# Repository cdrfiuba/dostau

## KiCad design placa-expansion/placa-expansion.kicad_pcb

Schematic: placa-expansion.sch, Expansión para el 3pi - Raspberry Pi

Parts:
C1: 2.2uF
C2: 330uF
D1: LED
J1: PBD-26
JP1: JUMPER
P1: BATT
P2: CONN_3PI
P3: PWR_HUB
P4: PWR_3pi
P5, P6, P7, P8: CONN_4
R1: 21k
R2: 330
U1: PTN78020
U?1: TXB0108

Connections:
+5V: C2.1, J1.2 (5v), P3.2 (PM), P5.1, P6.1, P7.1, P8.1, U1.5 (Vos), U1.6 (VO)
+BATT: C1.1, P1.2 (PM), P4.2 (PM), U1.2 (VI)
/3v3_rPi: J1.1 (3v3), U?1.2 (VCCA), U?1.10 (OE)
/AD6: P2.8, P5.3, U?1.17 (B3)
/AD6_rPi: J1.11 (GPIO17), U?1.4 (A3)
/AD7: P2.10, P6.3, U?1.16 (B4)
/AD7_rPi: J1.13 (GPIO21), U?1.5 (A4)
/Echo3: P2.12, P7.3, U?1.15 (B5)
/Echo4: P2.11, P8.3, U?1.14 (B6)
/LED: J1.23 (GPIO11/SCLK), U?1.9 (A8)
/PB3_rPi: J1.21 (GPIO9/MISO), U?1.8 (A7)
/PC5_rPi: J1.15 (GPIO22), U?1.6 (A5)
/PC6: P2.9, P5.2, P6.2, P7.2, P8.2, U?1.13 (B7)
/PC6_rPi: J1.19 (GPIO10/MOSI), U?1.7 (A6)
/RX_3pi: P2.4, U?1.20 (B1)
/RX_rPi: J1.10 (GPIO15/Rx), U?1.3 (A2)
/TX_3pi: P2.6, U?1.18 (B2)
/VBoost: P2.3
/Vbat_3pi: P2.5
/Vcc_3pi: P2.7, U?1.19 (VCCB)
GND: C1.2, C2.2, J1.6 (GND), JP1.2, P1.1, P2.1, P2.2, P2.13, P2.14, P3.1, P4.1, P5.4, P6.4, P7.4, P8.4, R2.1, U1.1 (GND), U?1.11 (GND)
unnamed: R1.2, U1.4 (set1)
unnamed: R1.1, U1.7 (GND)
unnamed: D1.2 (K), R2.2
unnamed: D1.1 (A), U?1.12 (B8)
unnamed: JP1.1, U1.3 (Inhibit)

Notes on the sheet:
Conector rPi
HC-SR04 UltraSound Pingers
3pi expansion
Fuente

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
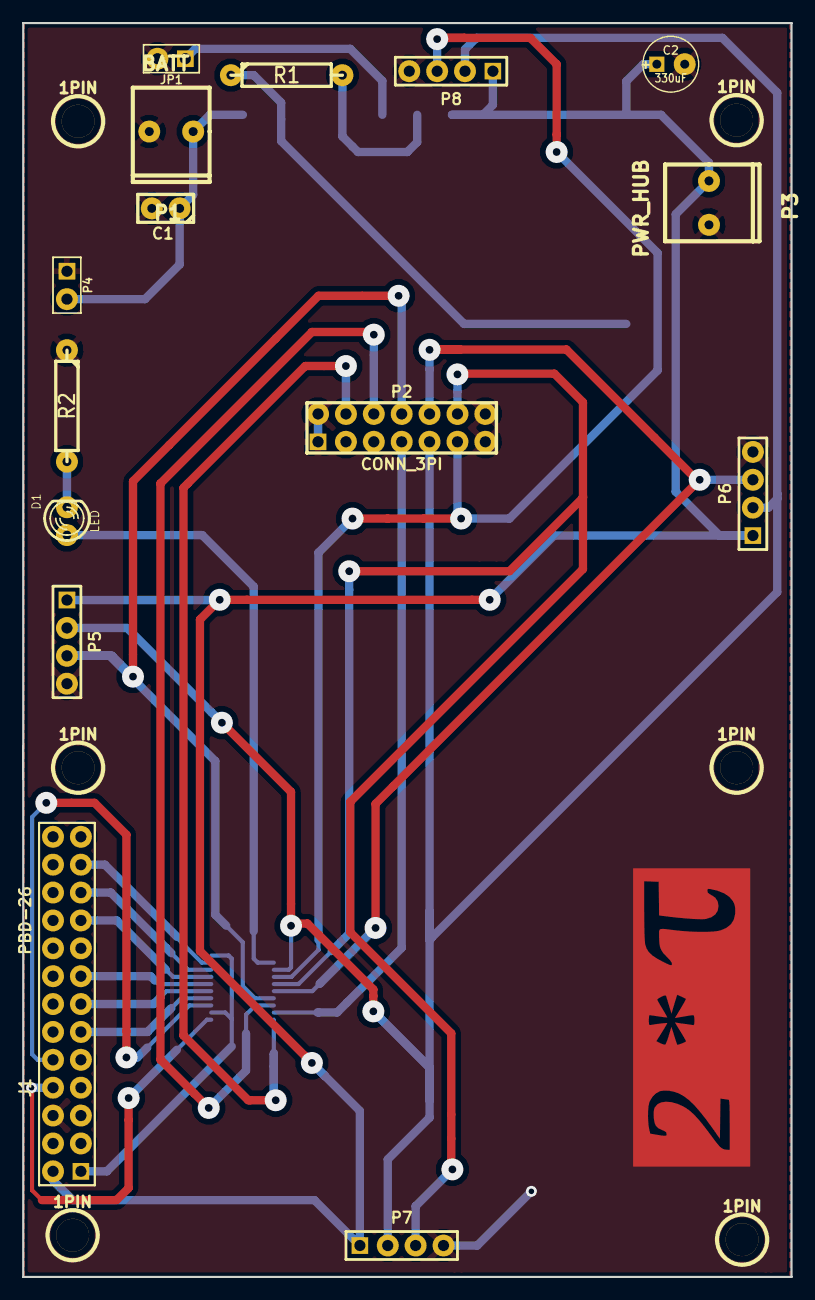
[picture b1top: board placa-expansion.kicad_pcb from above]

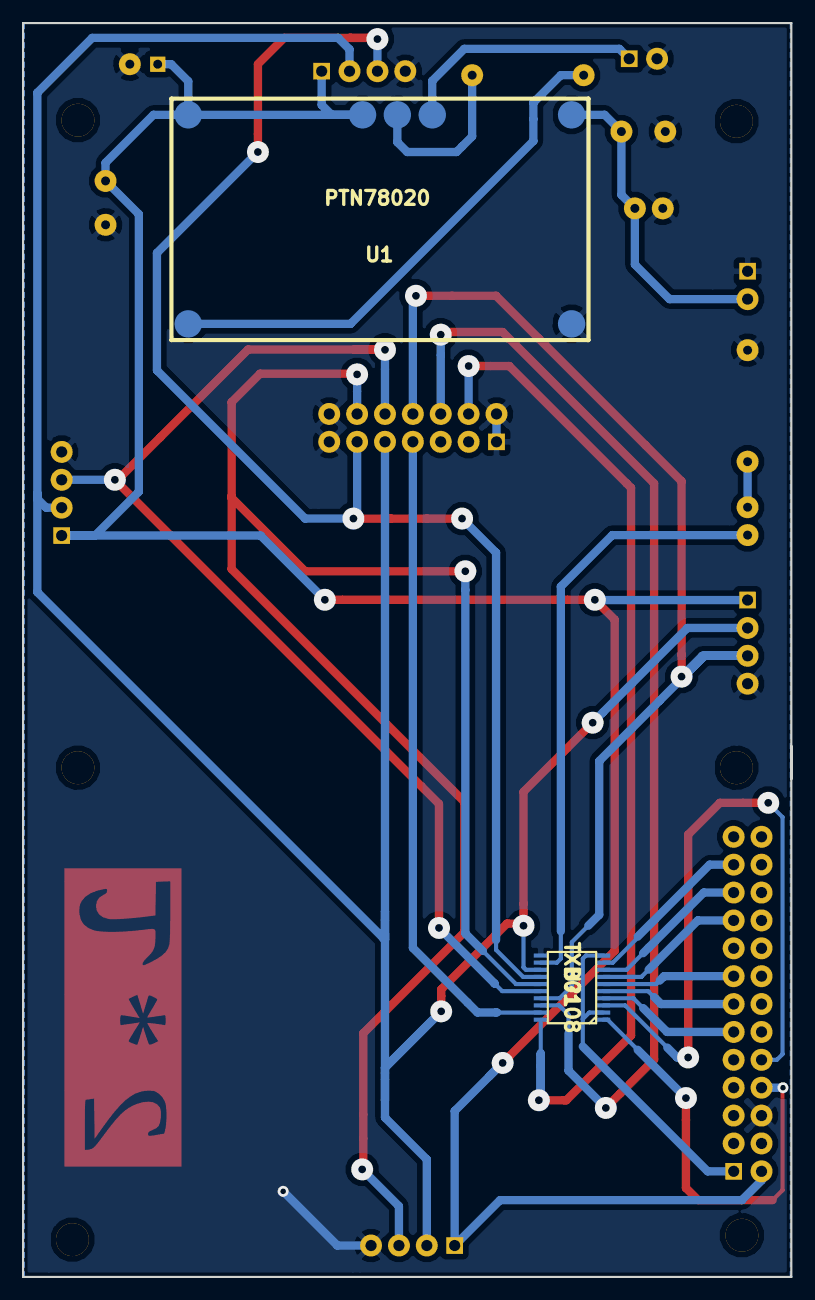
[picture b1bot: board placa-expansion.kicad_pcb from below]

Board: 2 copper layers, 70.0 x 114.2 mm, 23 parts (2 on the bottom side), 25 nets.

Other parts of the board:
1PIN, 1PIN#2, 1PIN#3, 1PIN#4, 1PIN#5, 1PIN#6: P***; 1pin

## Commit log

2013-04-21 Creo el proyecto de Kicad y agrego el componente con el conector de la rPi.
2013-04-26 Se incluye los ejemplos de pololu para el 3pi. El micro es el avr328p y el ejemplo utilizar es 3pi-demo-or-serial-slave
2013-04-27 Agregamos los conectores al esquematico.
    Falta poner la interfaz en los pines Tx y Rx entre el 3pi y el rPi.
    Falta tambien agregar el regulador para la rPi.
2013-04-27 El driver que utilizaremos para interfacear el rPi con el 3pi es el TXB0108
2013-05-04 Se trabajo sobre el esquemático
    Se agrego el integrado buffer y el regulador de 5V para la rPi
2013-05-10 Revisamos el esquematico.
    Faltan agregar los sensores.
2013-05-11 Terminamos el esquemático. Saco dos archivos que no tenian que estar.
2013-05-11 Asociamos los componentes del esquematico a su footprint
2013-05-11 Agregamos los footprint del regulador de texas
2013-05-18 Se terminó de asignar los footprints a todos los componentes y se comenzó con el ruteo de la placa
2013-05-25 Agrego el principio de la implementacion del protocolo para comunicarse con el 3pi desde la rPi usando el puerto serie.
2013-05-26 Agrego el .hgignore.
2013-05-26 Casi terminado el modulo de comunicacion serie con el 3pi. Faltan las funciones que leen datos del auto.
2013-05-26 Renombre la biblioteca a Py3pi en lugar de m3pi.
2013-05-26 Completo la implementacion del protocolo. Hay unos cuentos tests pero faltan algunos. 89% de coverage.
2013-05-26 Empaqueto el modulo de comunicacion serie con dist-utils para simplificar su posterior uso.
2013-05-29 Renombro src a Py3pi.
2013-05-29 Agrego imagenes de prueba y archivos de segmentos correspondientes. Agregamos clase python de lineas.
2013-05-29 Agrego un experimento para procesar los segmentos de lineas.
2013-05-30 Ordeno los vértices de cada segmento según su coordenada Y para que tengan coherencia los ángulos.
2013-05-30 Invierto el ordenamiento de los segmentos para que sea coherente con el sistema de coordenadas de la imagen.
2013-06-01 Comienzamos a rutear la placa interfaz
2013-06-01 Pequeña modificacion en el pcb
2013-06-01 Hice un reproductor de MPEG con pygame para probar la detección de lineas en tiempo real.
2013-06-01 Primera prueba de reconocimiento de líneas en el video y mediana de los ángulos para estimar la dirección.
2013-06-01 Agrego el modulo de Python que wrappea la libreria LSD para evitar tener que pasar por archivos para procesar las imagenes. Todavia no anda.
2013-06-02 Arreglo el modulo en C. El problema estaba en que no estaba forzando numpy a usar doubles cuando convertia los datos de la foto a un arreglo de np. Por este motivo, C interpretaba cualquier fruta en 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
2013-06-02 Completo el modulo de Python que wrappea LSD. Por ahora el unico metodo que tiene abre un archivo de imagen. Hay que ver de que forma necesitamos pasar la imagen y crear el metodo correspondiente. Ha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
2013-06-02 Actualizo el hgignore. Agrego el logo del proyecto.
2013-06-02 Modifico el testo del video para usar el wrapper python para LSD.
2013-06-02 Agrego metodos al wrapper para escribir el archivo igual al que genera LSD y para buscar los segmentos a partir de la lista de pixels. Actualizo el test.
2013-06-02 Agrego all como dependencia al install en el Makefile de pylsd.
2013-06-02 Agrego codigo para renderizar videos de prueba con el indicador de dirección.
2013-06-02 Agrego extensiones de video .mpg .avi al hgignore.
2013-06-03 Cambio el ejemplo de prueba con video para usar el wrapper de LSD en python.
2013-06-03 placa routeada
2013-06-03 agregue texto a la placa
2013-06-03 Cambio el constructor de Line para que se pueda crear usando la lista de números en lugar del string. Ahora no es necesario pasar por ningún archivo ni hacer cambios entre string y números. Debería s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
2013-06-03 Cambio el codigo del testAngles para que use el nuevo constructor de Line.
2013-09-28 Borro las pistas y agrando los pads.
2013-09-28 subo placa rooteada. Faltaría revisión.
2013-09-28 subo logo a la placa
2013-09-29 El pin 7 del conector de la rpi estaba mal conectado
2013-09-29 subo nueva version del diseño del pcb, corregido J1
2013-09-29 modifico un par de pistas
2013-09-29 subo archivos de fabricacion para el LCI, capas: drill, soldermask y copper
2013-09-29 subo zip para fabricacion y elimino algunos archivo inecesarios
2013-10-03 subo achivos para panelizacion
2013-10-17 subo .brd
